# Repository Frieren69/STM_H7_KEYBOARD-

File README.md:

# STM_H7_KEYBOARD-
An keyboard with STM 32H7

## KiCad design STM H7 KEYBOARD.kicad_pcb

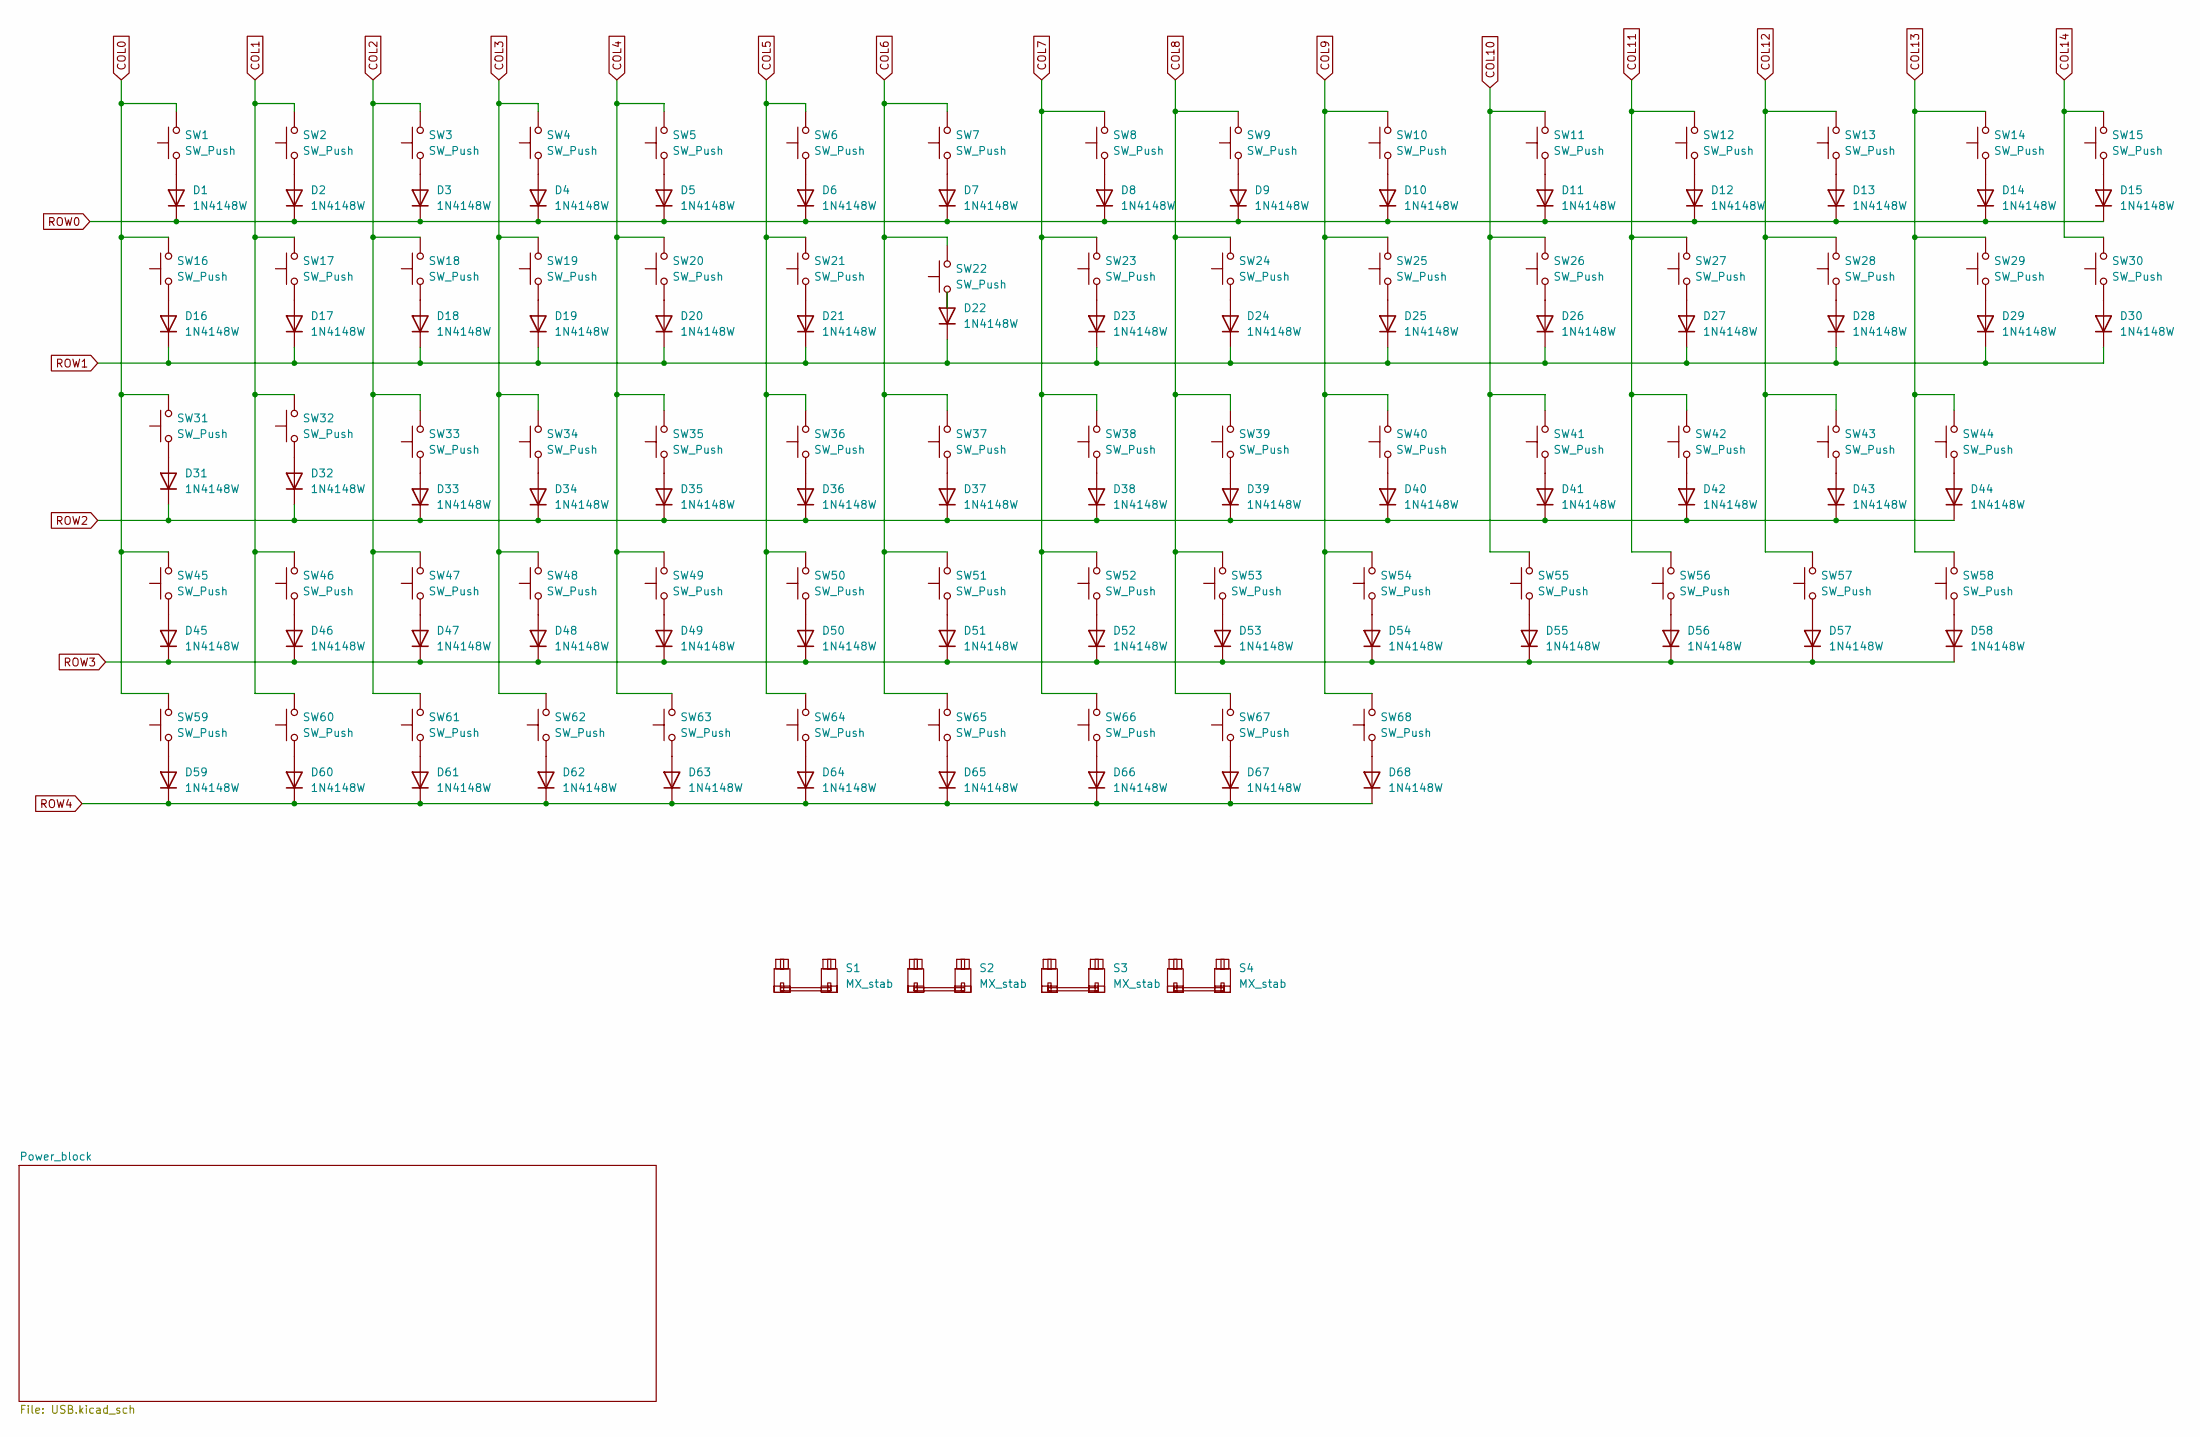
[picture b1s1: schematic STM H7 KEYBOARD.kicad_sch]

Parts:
D1, D2, D3, D4, D5, D6, D7, D8, D9, D10, D11, D12, D13, D14, D15, D16, D17, D18, D19, D20, D21, D22, D23, D24, D25, D26, D27, D28, D29, D30, D31, D32, D33, D34, D35, D36, D37, D38, D39, D40, D41, D42, D43, D44, D45, D46, D47, D48, D49, D50, D51, D52, D53, D54, D55, D56, D57, D58, D59, D60, D61, D62, D63, D64, D65, D66, D67, D68: 1N4148W; D_SOD-123
S1: MX_stab; STAB_MX_P_6.25u
S2, S3, S4: MX_stab; STAB_MX_P_2u
SW1, SW2, SW3, SW4, SW5, SW6, SW7, SW8, SW9, SW10, SW11, SW12, SW13, SW14, SW15, SW16, SW17, SW18, SW19, SW20, SW21, SW22, SW23, SW24, SW25, SW26, SW27, SW28, SW29, SW30, SW31, SW32, SW33, SW34, SW35, SW36, SW37, SW38, SW39, SW40, SW41, SW42, SW43, SW44, SW45, SW46, SW47, SW48, SW49, SW50, SW51, SW52, SW53, SW54, SW55, SW56, SW57, SW58, SW59, SW60, SW61, SW62, SW63, SW64, SW65, SW66, SW67, SW68: SW_Push; SW_MX_Hotswap_C49352235_5Pin

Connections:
COL0: SW1.2, SW16.2, SW31.2, SW45.2, SW59.2; also elsewhere on the board
COL2: SW3.2, SW18.2, SW33.2, SW47.2, SW61.2; also elsewhere on the board
COL3: SW4.2, SW19.2, SW34.2, SW48.2, SW62.2; also elsewhere on the board
COL4: SW5.2, SW20.2, SW35.2, SW49.2, SW63.2; also elsewhere on the board
COL5: SW6.2, SW21.2, SW36.2, SW50.2, SW64.2; also elsewhere on the board
COL6: SW7.2, SW22.2, SW37.2, SW51.2, SW65.2; also elsewhere on the board
COL7: SW8.2, SW23.2, SW38.2, SW52.2, SW66.2; also elsewhere on the board
COL8: SW9.2, SW24.2, SW39.2, SW53.2, SW67.2; also elsewhere on the board
COL9: SW10.2, SW25.2, SW40.2, SW54.2, SW68.2; also elsewhere on the board
COL10: SW11.2, SW26.2, SW41.2, SW55.2; also elsewhere on the board
COL11: SW12.2, SW27.2, SW42.2, SW56.2; also elsewhere on the board
COL12: SW13.2, SW28.2, SW43.2, SW57.2; also elsewhere on the board
COL13: SW14.2, SW29.2, SW44.2, SW58.2; also elsewhere on the board
COL14: SW15.2, SW30.2; also elsewhere on the board
unnamed: D1.2 (A), SW1.1
unnamed: D2.2 (A), SW2.1
unnamed: D3.2 (A), SW3.1
unnamed: D4.2 (A), SW4.1
unnamed: D5.2 (A), SW5.1
unnamed: D6.2 (A), SW6.1
unnamed: D7.2 (A), SW7.1
unnamed: D8.2 (A), SW8.1
unnamed: D9.2 (A), SW9.1
unnamed: D10.2 (A), SW10.1
unnamed: D11.2 (A), SW11.1
unnamed: D12.2 (A), SW12.1
unnamed: D13.2 (A), SW13.1
unnamed: D14.2 (A), SW14.1
unnamed: D15.2 (A), SW15.1
unnamed: D16.2 (A), SW16.1
unnamed: D17.2 (A), SW17.1
unnamed: D18.2 (A), SW18.1
unnamed: D19.2 (A), SW19.1
unnamed: D20.2 (A), SW20.1
unnamed: D21.2 (A), SW21.1
unnamed: D22.2 (A), SW22.1
unnamed: D23.2 (A), SW23.1
unnamed: D24.2 (A), SW24.1
unnamed: D25.2 (A), SW25.1
unnamed: D26.2 (A), SW26.1
unnamed: D27.2 (A), SW27.1
unnamed: D28.2 (A), SW28.1
unnamed: D29.2 (A), SW29.1
unnamed: D30.2 (A), SW30.1
unnamed: D31.2 (A), SW31.1
unnamed: D32.2 (A), SW32.1
unnamed: D33.2 (A), SW33.1
unnamed: D34.2 (A), SW34.1
unnamed: D35.2 (A), SW35.1
unnamed: D36.2 (A), SW36.1
unnamed: D37.2 (A), SW37.1
unnamed: D38.2 (A), SW38.1
unnamed: D39.2 (A), SW39.1
unnamed: D40.2 (A), SW40.1
unnamed: D41.2 (A), SW41.1
unnamed: D42.2 (A), SW42.1
unnamed: D43.2 (A), SW43.1
unnamed: D44.2 (A), SW44.1
unnamed: D45.2 (A), SW45.1
unnamed: D46.2 (A), SW46.1
unnamed: D47.2 (A), SW47.1
unnamed: D48.2 (A), SW48.1
unnamed: D49.2 (A), SW49.1
unnamed: D50.2 (A), SW50.1
unnamed: D51.2 (A), SW51.1
unnamed: D52.2 (A), SW52.1
unnamed: D53.2 (A), SW53.1
unnamed: D54.2 (A), SW54.1
unnamed: D55.2 (A), SW55.1
unnamed: D56.2 (A), SW56.1
unnamed: D57.2 (A), SW57.1
unnamed: D58.2 (A), SW58.1
unnamed: D59.2 (A), SW59.1
unnamed: D61.2 (A), SW61.1
unnamed: D62.2 (A), SW62.1
unnamed: D63.2 (A), SW63.1
unnamed: D64.2 (A), SW64.1
unnamed: D65.2 (A), SW65.1
unnamed: D66.2 (A), SW66.1
unnamed: D67.2 (A), SW67.1
unnamed: D68.2 (A), SW68.1
ROW0: D1.1 (K), D2.1 (K), D3.1 (K), D4.1 (K), D5.1 (K), D6.1 (K), D7.1 (K), D8.1 (K), D9.1 (K), D10.1 (K), D11.1 (K), D12.1 (K), D13.1 (K), D14.1 (K), D15.1 (K); also elsewhere on the board
ROW1: D16.1 (K), D17.1 (K), D18.1 (K), D19.1 (K), D20.1 (K), D21.1 (K), D22.1 (K), D23.1 (K), D24.1 (K), D25.1 (K), D26.1 (K), D27.1 (K), D28.1 (K), D29.1 (K), D30.1 (K); also elsewhere on the board
ROW2: D31.1 (K), D32.1 (K), D33.1 (K), D34.1 (K), D35.1 (K), D36.1 (K), D37.1 (K), D38.1 (K), D39.1 (K), D40.1 (K), D41.1 (K), D42.1 (K), D43.1 (K), D44.1 (K); also elsewhere on the board
ROW3: D45.1 (K), D46.1 (K), D47.1 (K), D48.1 (K), D49.1 (K), D50.1 (K), D51.1 (K), D52.1 (K), D53.1 (K), D54.1 (K), D55.1 (K), D56.1 (K), D57.1 (K), D58.1 (K); also elsewhere on the board
ROW4: D59.1 (K), D60.1 (K), D61.1 (K), D62.1 (K), D63.1 (K), D64.1 (K), D65.1 (K), D66.1 (K), D67.1 (K), D68.1 (K); also elsewhere on the board

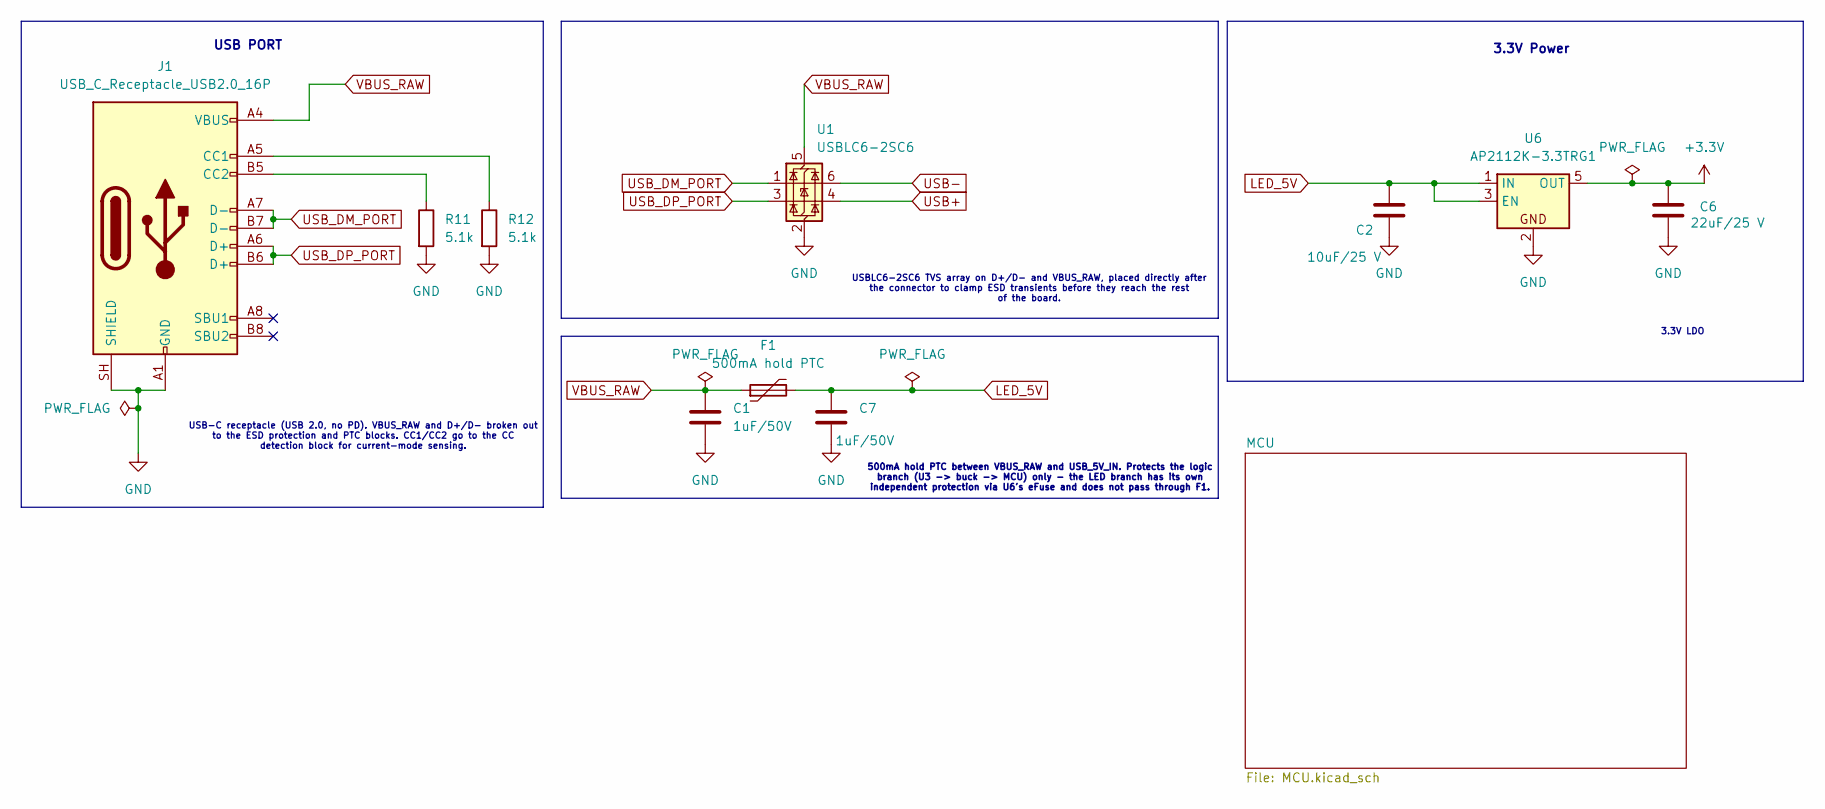
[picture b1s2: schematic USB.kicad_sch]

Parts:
C1, C7: 1uF/50V; C_0805_2012Metric
C2: 10uF/25 V; C_0805_2012Metric
C6: 22uF/25 V; C_0805_2012Metric
F1: 500mA hold PTC; Fuse_1206_3216Metric
J1: USB_C_Receptacle_USB2.0_16P; USB_C_Receptacle_HRO_TYPE-C-31-M-12
R11, R12: 5.1k; R_0603_1608Metric
U1: USBLC6-2SC6; SOT-23-6
U6: AP2112K-3.3TRG1; SOT-23-5

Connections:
+3.3V: C6.1, U6.5 (OUT); also elsewhere on the board
LED_5V: C2.1, C7.1, F1.2, U6.1 (IN), U6.3 (EN); also elsewhere on the board
unnamed: J1.A5 (CC1), R12.1
unnamed: J1.B5 (CC2), R11.1
USB+: U1.4 (I/O2); also elsewhere on the board
USB-: U1.6 (I/O1); also elsewhere on the board
USB_DM_PORT: J1.A7 (D-), J1.B7 (D-), U1.1 (I/O1)
USB_DP_PORT: J1.A6 (D+), J1.B6 (D+), U1.3 (I/O2)
VBUS_RAW: C1.1, F1.1, J1.A4 (VBUS), J1.A9 (VBUS), J1.B4 (VBUS), J1.B9 (VBUS), U1.5 (VBUS)

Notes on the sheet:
USBLC6-2SC6 TVS array on D+/D- and VBUS_RAW, placed directly after the connector to clamp ESD transients before they reach the rest of the board.
USB-C receptacle (USB 2.0, no PD). VBUS_RAW and D+/D- broken out to the ESD protection and PTC blocks. CC1/CC2 go to the CC detection block for current-mode sensing.
USB PORT
3.3V Power
500mA hold PTC between VBUS_RAW and USB_5V_IN. Protects the logic branch (U3 -> buck -> MCU) only - the LED branch has its own independent protection via U6's eFuse and does not pass through F1.
3.3V LDO

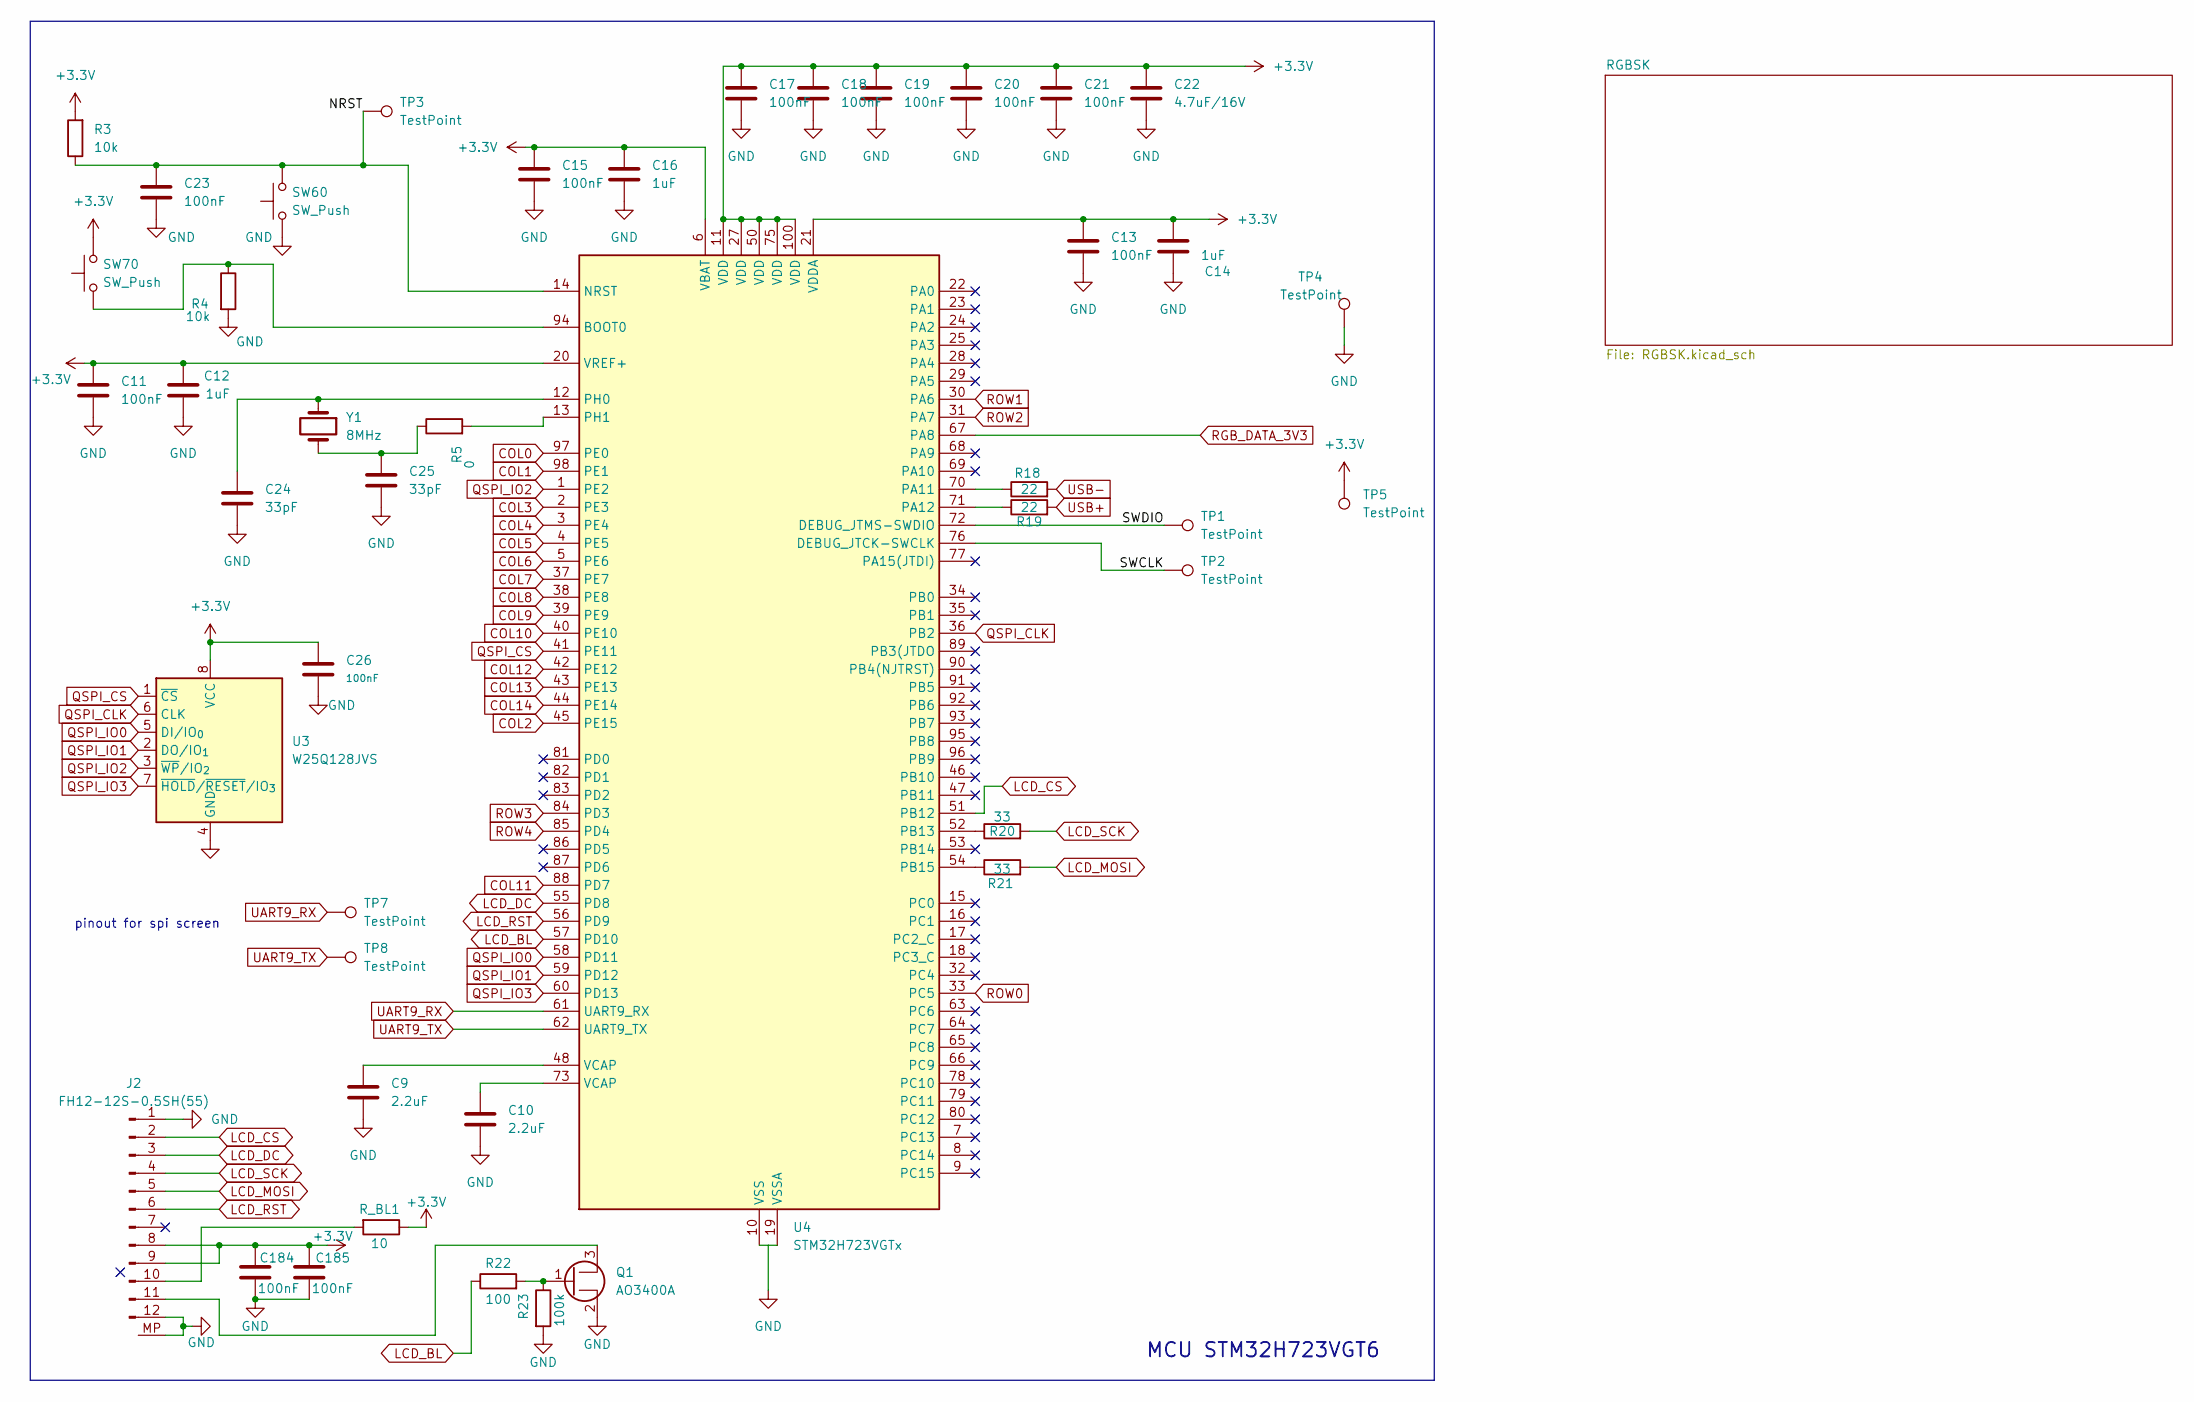
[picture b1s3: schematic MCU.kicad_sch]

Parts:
C9, C10: 2.2uF; C_0603_1608Metric
C11, C13, C15, C17, C18, C19, C20, C21, C23: 100nF; C_0603_1608Metric
C12, C14, C16: 1uF; C_0805_2012Metric
C22: 4.7uF/16V; C_0603_1608Metric
C24, C25: 33pF; C_0603_1608Metric
C26: 100nF; C_0402_1005Metric
C184, C185: 100nF; C_0402_1005Metric; LCSC C1525
J2: FH12-12S-0.5SH(55); Hirose_FH12-12S-0.5SH_1x12-1MP_P0.50mm_Horizontal; LCSC C88360
Q1: AO3400A; SOT-23; LCSC C20917
R3, R4: 10k; R_0603_1608Metric
R5: 0; R_0603_1608Metric
R18, R19: 22; R_0603_1608Metric
R20, R21: 33; R_0402_1005Metric; LCSC C25106
R22: 100; R_0402_1005Metric; LCSC C25076
R23: 100k; R_0402_1005Metric; LCSC C25741
R_BL1: 10; R_0603_1608Metric; LCSC C22859
SW60, SW70: SW_Push; SW_SPST_TL3342
TP1, TP2, TP3, TP4, TP5, TP7, TP8: TestPoint; TestPoint_Pad_D2.0mm
U3: W25Q128JVS; SOIC-8_5.3x5.3mm_P1.27mm; LCSC C97521
U4: STM32H723VGTx; LQFP-100_14x14mm_P0.5mm; LCSC C730142
Y1: 8MHz; Crystal_SMD_5032-2Pin_5.0x3.2mm; LCSC C115962

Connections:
+3.3V: C11.1, C12.1, C13.1, C14.1, C15.1, C16.1, C17.1, C18.1, C19.1, C20.1, C21.1, C22.1, C26.1, C184.1, C185.1, J2.8 (IOVCC), J2.9 (VCC), R3.2, R_BL1.1, TP5.1 (1_1), U3.8 (VCC), U4.6 (VBAT), U4.11 (VDD), U4.20 (VREF+), U4.21 (VDDA), U4.27 (VDD), U4.50 (VDD), U4.75 (VDD), U4.100 (VDD); also elsewhere on the board
/Power_block/MCU/SWCLK: TP2.1 (1_1), U4.76 (DEBUG_JTCK-SWCLK)
/Power_block/MCU/SWDIO: TP1.1 (1_1), U4.72 (DEBUG_JTMS-SWDIO)
COL0: U4.97 (PE0); also elsewhere on the board
COL2: U4.45 (PE15); also elsewhere on the board
COL3: U4.2 (PE3); also elsewhere on the board
COL4: U4.3 (PE4); also elsewhere on the board
COL5: U4.4 (PE5); also elsewhere on the board
COL6: U4.5 (PE6); also elsewhere on the board
COL7: U4.37 (PE7); also elsewhere on the board
COL8: U4.38 (PE8); also elsewhere on the board
COL9: U4.39 (PE9); also elsewhere on the board
COL10: U4.40 (PE10); also elsewhere on the board
COL11: U4.88 (PD7); also elsewhere on the board
COL12: U4.42 (PE12); also elsewhere on the board
COL13: U4.43 (PE13); also elsewhere on the board
COL14: U4.44 (PE14); also elsewhere on the board
LCD_BL: R22.1, U4.57 (PD10)
LCD_CS: J2.2 (CS), U4.51 (PB12)
LCD_DC: J2.3 (RS), U4.55 (PD8)
LCD_MOSI: J2.5 (SDA), R21.2
LCD_RST: J2.6 (RST), U4.56 (PD9)
LCD_SCK: J2.4 (SCL), R20.2
unnamed: C9.1, U4.48 (VCAP)
unnamed: C10.1, U4.73 (VCAP)
unnamed: C25.1, R5.1, Y1.2
unnamed 164: J2.10 (LEDA), R_BL1.2; also elsewhere on the board
unnamed: J2.11 (LEDK), Q1.3 (D)
unnamed: Q1.1 (G), R22.2, R23.1
unnamed 168: R4.1, U4.94 (BOOT0); also elsewhere on the board
unnamed: R18.1, U4.70 (PA11)
unnamed: R19.1, U4.71 (PA12)
unnamed: R20.1, U4.52 (PB13)
unnamed: R21.1, U4.54 (PB15)
unnamed: C24.1, U4.12 (PH0), Y1.1
unnamed: R5.2, U4.13 (PH1)
QSPI_CLK: U3.6 (CLK), U4.36 (PB2)
QSPI_CS: U3.1 (~CS), U4.41 (PE11)
QSPI_IO0: U3.5 (DI/IO_{0}), U4.58 (PD11)
QSPI_IO1: U3.2 (DO/IO_{1}), U4.59 (PD12)
QSPI_IO2: U3.3 (~WP/IO_{2}), U4.1 (PE2)
QSPI_IO3: U3.7 (~HOLD/~RESET/IO_{3}), U4.60 (PD13)
RGB_DATA_3V3: U4.67 (PA8); also elsewhere on the board
ROW0: U4.33 (PC5); also elsewhere on the board
ROW1: U4.30 (PA6); also elsewhere on the board
ROW2: U4.31 (PA7); also elsewhere on the board
ROW3: U4.84 (PD3); also elsewhere on the board
ROW4: U4.85 (PD4); also elsewhere on the board
UART9_RX: TP7.1 (1_1), U4.61 (UART9_RX)
UART9_TX: TP8.1 (1_1), U4.62 (UART9_TX)
USB+: R19.2; also elsewhere on the board
USB-: R18.2; also elsewhere on the board

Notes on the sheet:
pinout for spi screen
MCU STM32H723VGT6

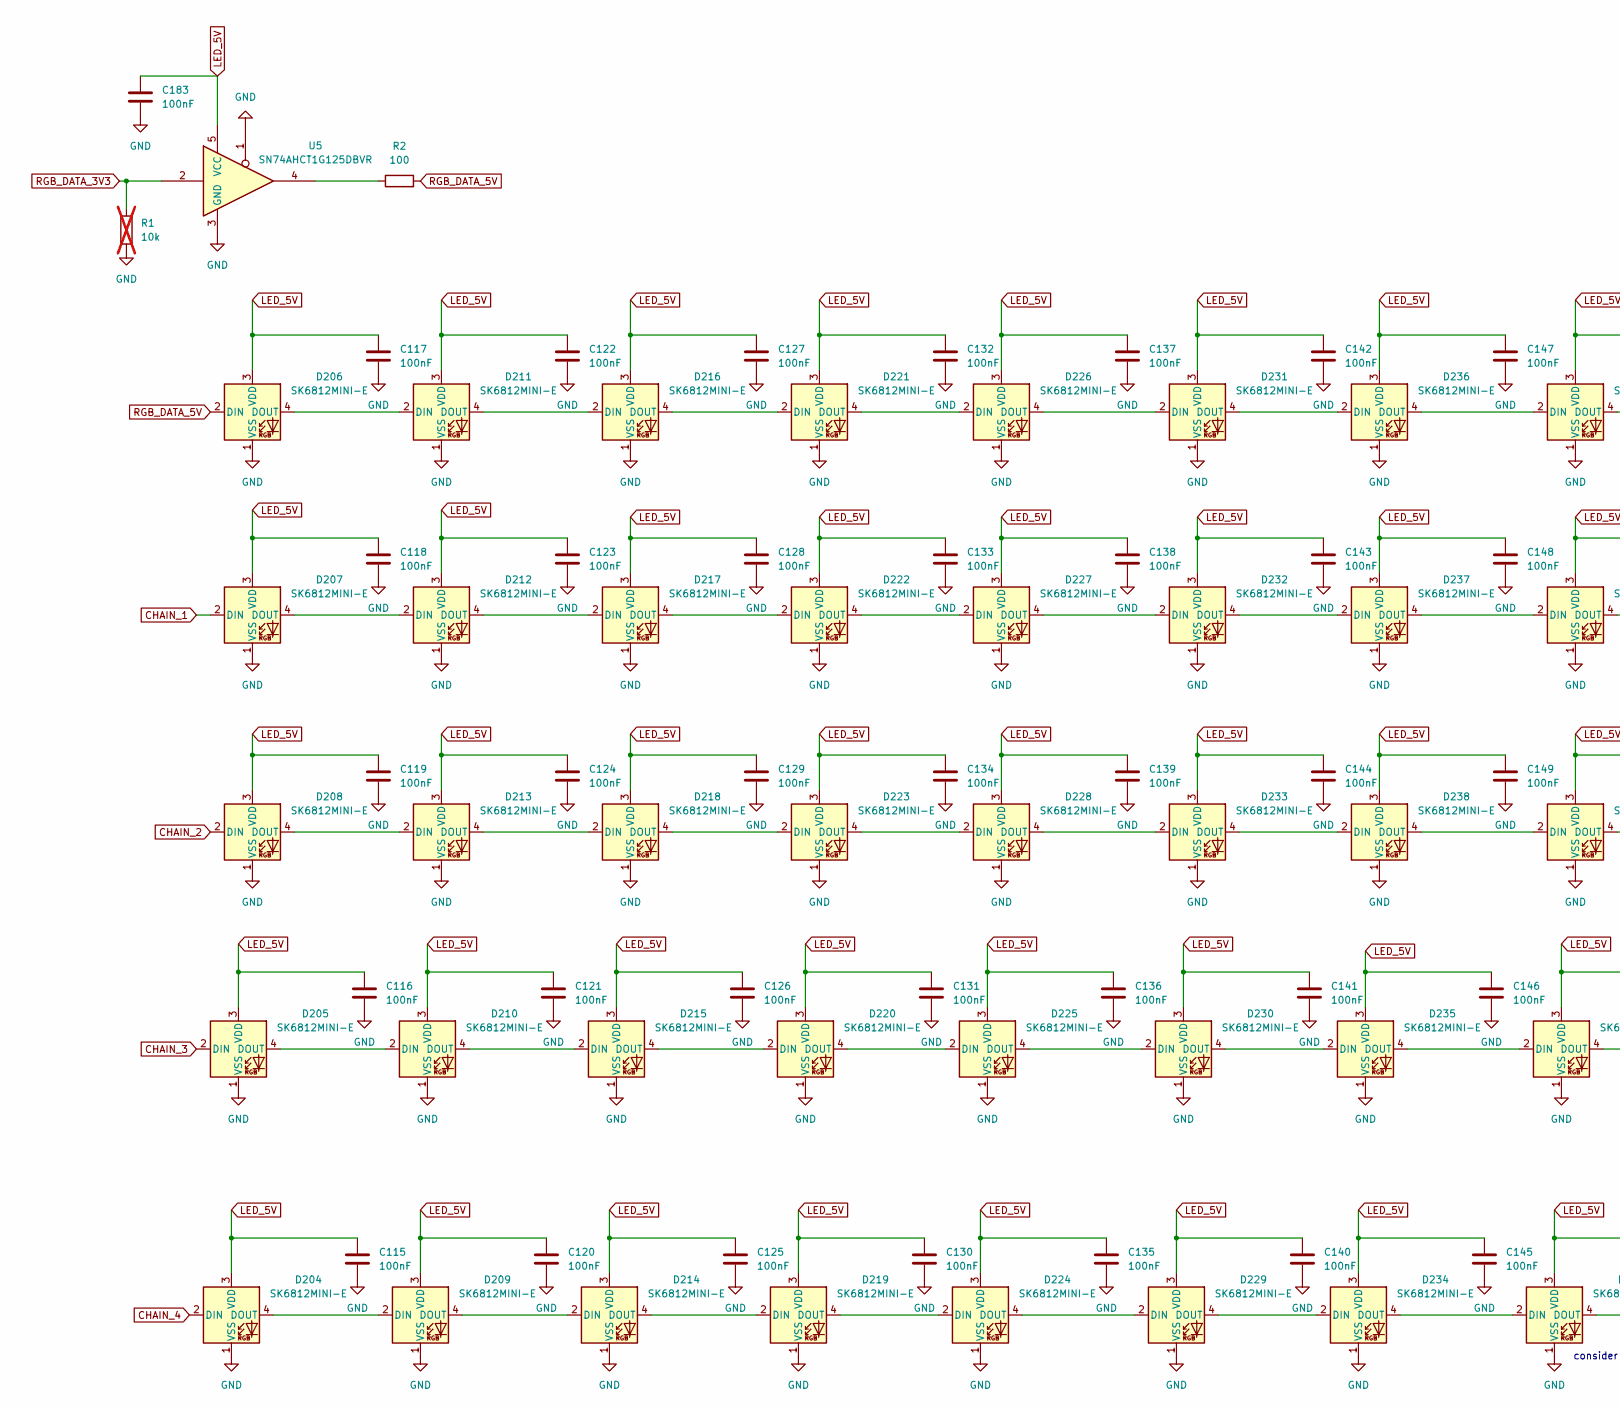
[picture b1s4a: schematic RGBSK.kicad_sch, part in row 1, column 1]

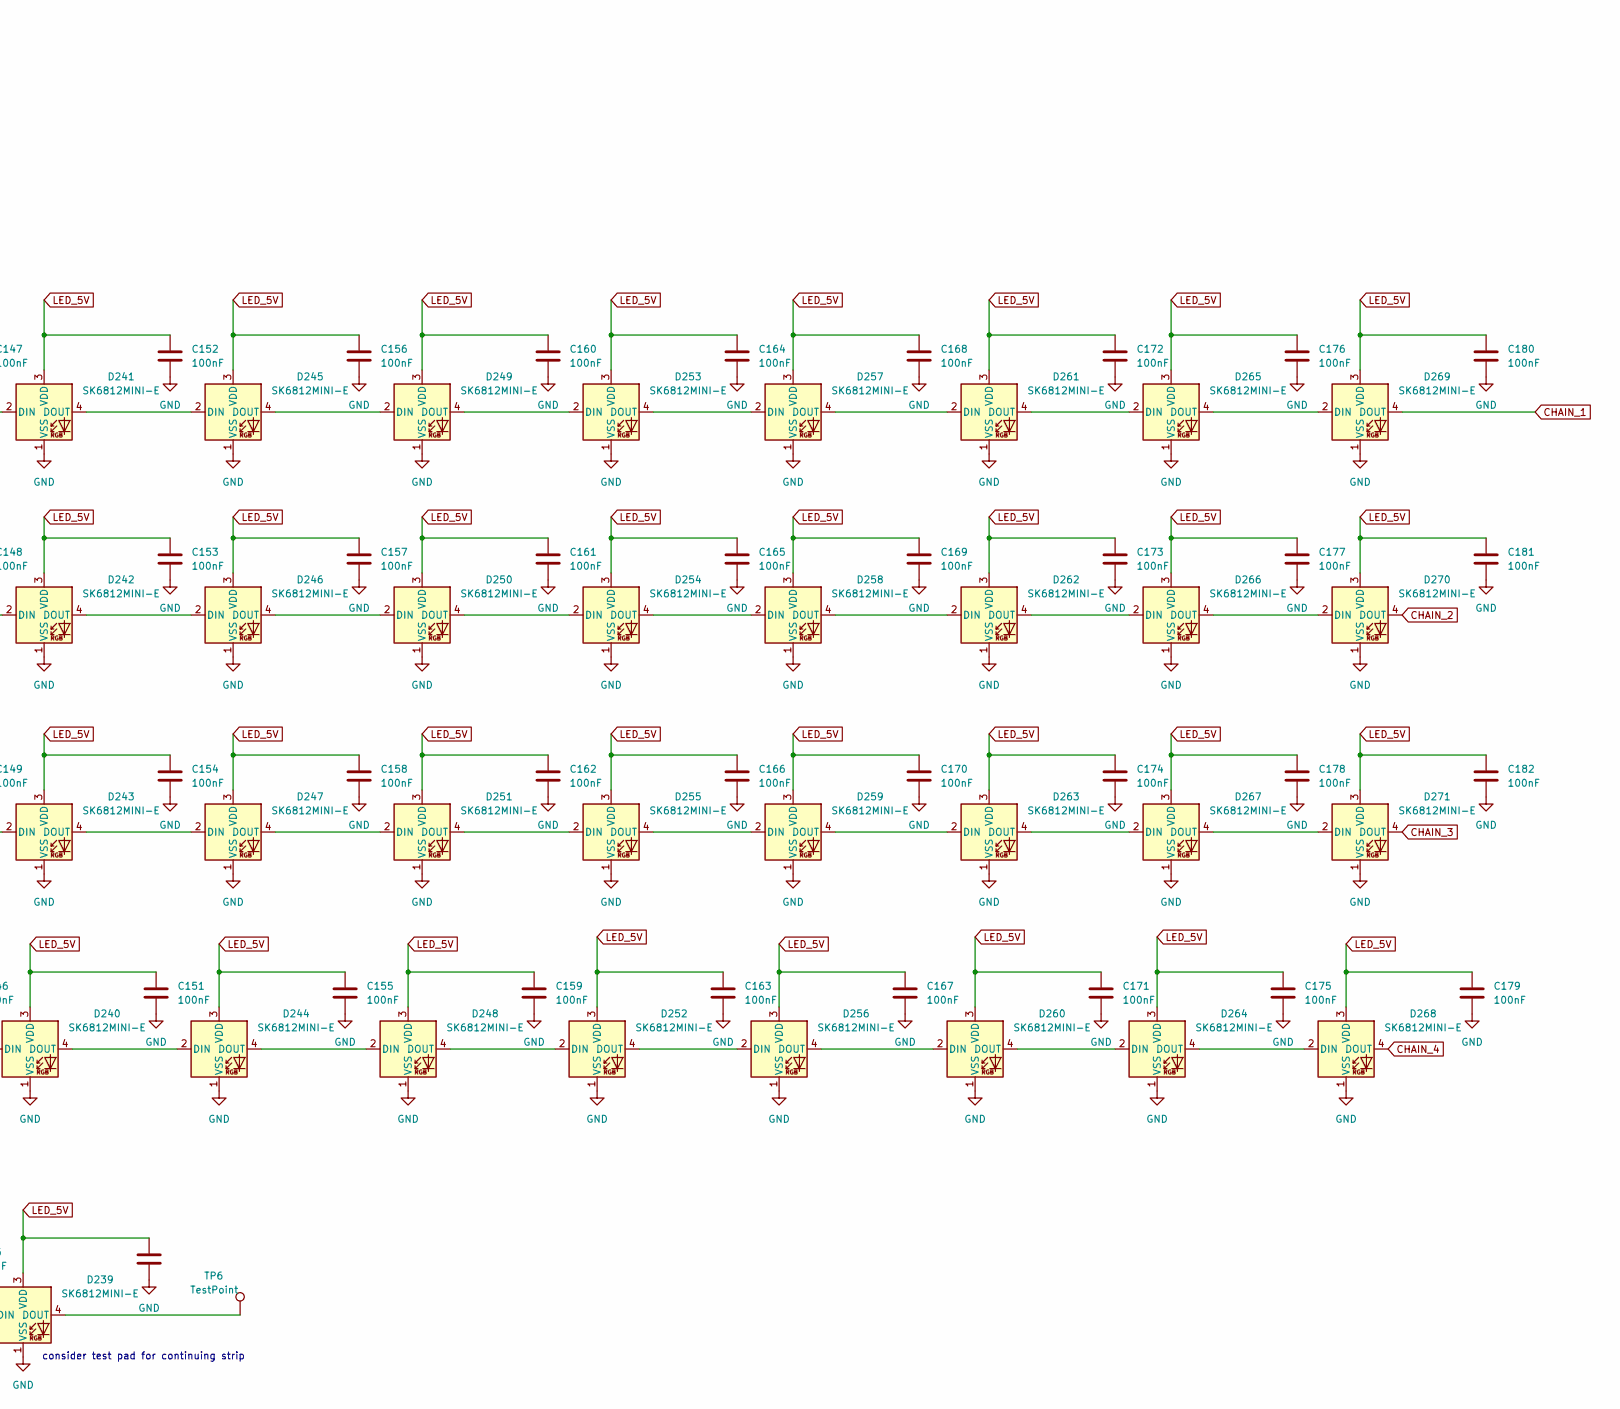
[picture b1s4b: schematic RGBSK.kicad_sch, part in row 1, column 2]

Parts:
C115, C116, C117, C118, C119, C120, C121, C122, C123, C124, C125, C126, C127, C128, C129, C130, C131, C132, C133, C134, C135, C136, C137, C138, C139, C140, C141, C142, C143, C144, C145, C146, C147, C148, C149, C150, C151, C152, C153, C154, C155, C156, C157, C158, C159, C160, C161, C162, C163, C164, C165, C166, C167, C168, C169, C170, C171, C172, C173, C174, C175, C176, C177, C178, C179, C180, C181, C182, C183: 100nF; C_0402_1005Metric
D204, D205, D206, D207, D208, D209, D210, D211, D212, D213, D214, D215, D216, D217, D218, D219, D220, D221, D222, D223, D224, D225, D226, D227, D228, D229, D230, D231, D232, D233, D234, D235, D236, D237, D238, D239, D240, D241, D242, D243, D244, D245, D246, D247, D248, D249, D250, D251, D252, D253, D254, D255, D256, D257, D258, D259, D260, D261, D262, D263, D264, D265, D266, D267, D268, D269, D270, D271: SK6812MINI-E; LED_SK6812MINI-E_3.2x2.8mm_P1.5mm_ReverseMount
R1: 10k; R_0402_1005Metric; not fitted
R2: 100; R_0402_1005Metric
TP6: TestPoint; TestPoint_Pad_D2.0mm
U5: SN74AHCT1G125DBVR; SOT-23-5

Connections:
CHAIN_1: D207.2 (DIN), D269.4 (DOUT)
CHAIN_2: D208.2 (DIN), D270.4 (DOUT)
CHAIN_3: D205.2 (DIN), D271.4 (DOUT)
CHAIN_4: D204.2 (DIN), D268.4 (DOUT)
LED_5V: C115.1, C116.1, C117.1, C118.1, C119.1, C120.1, C121.1, C122.1, C123.1, C124.1, C125.1, C126.1, C127.1, C128.1, C129.1, C130.1, C131.1, C132.1, C133.1, C134.1, C135.1, C136.1, C137.1, C138.1, C139.1, C140.1, C141.1, C142.1, C143.1, C144.1, C145.1, C146.1, C147.1, C148.1, C149.1, C150.1, C151.1, C152.1, C153.1, C154.1, C155.1, C156.1, C157.1, C158.1, C159.1, C160.1, C161.1, C162.1, C163.1, C164.1, C165.1, C166.1, C167.1, C168.1, C169.1, C170.1, C171.1, C172.1, C173.1, C174.1, C175.1, C176.1, C177.1, C178.1, C179.1, C180.1, C181.1, C182.1, C183.1, D204.3 (VDD), D205.3 (VDD), D206.3 (VDD), D207.3 (VDD), D208.3 (VDD), D209.3 (VDD), D210.3 (VDD), D211.3 (VDD), D212.3 (VDD), D213.3 (VDD), D214.3 (VDD), D215.3 (VDD), D216.3 (VDD), D217.3 (VDD), D218.3 (VDD), D219.3 (VDD), D220.3 (VDD), D221.3 (VDD), D222.3 (VDD), D223.3 (VDD), D224.3 (VDD), D225.3 (VDD), D226.3 (VDD), D227.3 (VDD), D228.3 (VDD), D229.3 (VDD), D230.3 (VDD), D231.3 (VDD), D232.3 (VDD), D233.3 (VDD), D234.3 (VDD), D235.3 (VDD), D236.3 (VDD), D237.3 (VDD), D238.3 (VDD), D239.3 (VDD), D240.3 (VDD), D241.3 (VDD), D242.3 (VDD), D243.3 (VDD), D244.3 (VDD), D245.3 (VDD), D246.3 (VDD), D247.3 (VDD), D248.3 (VDD), D249.3 (VDD), D250.3 (VDD), D251.3 (VDD), D252.3 (VDD), D253.3 (VDD), D254.3 (VDD), D255.3 (VDD), D256.3 (VDD), D257.3 (VDD), D258.3 (VDD), D259.3 (VDD), D260.3 (VDD), D261.3 (VDD), D262.3 (VDD), D263.3 (VDD), D264.3 (VDD), D265.3 (VDD), D266.3 (VDD), D267.3 (VDD), D268.3 (VDD), D269.3 (VDD), D270.3 (VDD), D271.3 (VDD), U5.5 (VCC); also elsewhere on the board
unnamed: D204.4 (DOUT), D209.2 (DIN)
unnamed: D205.4 (DOUT), D210.2 (DIN)
unnamed: D207.4 (DOUT), D212.2 (DIN)
unnamed: D208.4 (DOUT), D213.2 (DIN)
unnamed: D209.4 (DOUT), D214.2 (DIN)
unnamed: D210.4 (DOUT), D215.2 (DIN)
unnamed 104: D206.4 (DOUT), D211.2 (DIN); also elsewhere on the board
unnamed: D211.4 (DOUT), D216.2 (DIN)
unnamed: D212.4 (DOUT), D217.2 (DIN)
unnamed: D213.4 (DOUT), D218.2 (DIN)
unnamed: D214.4 (DOUT), D219.2 (DIN)
unnamed: D215.4 (DOUT), D220.2 (DIN)
unnamed: D216.4 (DOUT), D221.2 (DIN)
unnamed: D217.4 (DOUT), D222.2 (DIN)
unnamed: D218.4 (DOUT), D223.2 (DIN)
unnamed: D219.4 (DOUT), D224.2 (DIN)
unnamed: D220.4 (DOUT), D225.2 (DIN)
unnamed: D221.4 (DOUT), D226.2 (DIN)
unnamed: D222.4 (DOUT), D227.2 (DIN)
unnamed: D223.4 (DOUT), D228.2 (DIN)
unnamed: D224.4 (DOUT), D229.2 (DIN)
unnamed: D225.4 (DOUT), D230.2 (DIN)
unnamed: D226.4 (DOUT), D231.2 (DIN)
unnamed: D227.4 (DOUT), D232.2 (DIN)
unnamed: D228.4 (DOUT), D233.2 (DIN)
unnamed: D229.4 (DOUT), D234.2 (DIN)
unnamed: D230.4 (DOUT), D235.2 (DIN)
unnamed: D231.4 (DOUT), D236.2 (DIN)
unnamed: D232.4 (DOUT), D237.2 (DIN)
unnamed: D233.4 (DOUT), D238.2 (DIN)
unnamed: D234.4 (DOUT), D239.2 (DIN)
unnamed: D235.4 (DOUT), D240.2 (DIN)
unnamed: D236.4 (DOUT), D241.2 (DIN)
unnamed: D237.4 (DOUT), D242.2 (DIN)
unnamed: D238.4 (DOUT), D243.2 (DIN)
unnamed: D239.4 (DOUT), TP6.1 (1_1)
unnamed: D240.4 (DOUT), D244.2 (DIN)
unnamed: D241.4 (DOUT), D245.2 (DIN)
unnamed: D242.4 (DOUT), D246.2 (DIN)
unnamed: D243.4 (DOUT), D247.2 (DIN)
unnamed: D244.4 (DOUT), D248.2 (DIN)
unnamed: D245.4 (DOUT), D249.2 (DIN)
unnamed: D246.4 (DOUT), D250.2 (DIN)
unnamed: D247.4 (DOUT), D251.2 (DIN)
unnamed: D248.4 (DOUT), D252.2 (DIN)
unnamed: D249.4 (DOUT), D253.2 (DIN)
unnamed: D250.4 (DOUT), D254.2 (DIN)
unnamed: D251.4 (DOUT), D255.2 (DIN)
unnamed: D252.4 (DOUT), D256.2 (DIN)
unnamed: D253.4 (DOUT), D257.2 (DIN)
unnamed: D254.4 (DOUT), D258.2 (DIN)
unnamed: D255.4 (DOUT), D259.2 (DIN)
unnamed: D256.4 (DOUT), D260.2 (DIN)
unnamed: D257.4 (DOUT), D261.2 (DIN)
unnamed: D258.4 (DOUT), D262.2 (DIN)
unnamed: D259.4 (DOUT), D263.2 (DIN)
unnamed: D260.4 (DOUT), D264.2 (DIN)
unnamed: D261.4 (DOUT), D265.2 (DIN)
unnamed: D262.4 (DOUT), D266.2 (DIN)
unnamed: D263.4 (DOUT), D267.2 (DIN)
unnamed: D264.4 (DOUT), D268.2 (DIN)
unnamed: D265.4 (DOUT), D269.2 (DIN)
unnamed: D266.4 (DOUT), D270.2 (DIN)
unnamed: D267.4 (DOUT), D271.2 (DIN)
unnamed: R2.1, U5.4
RGB_DATA_3V3: R1.1, U5.2; also elsewhere on the board
RGB_DATA_5V: D206.2 (DIN), R2.2; also elsewhere on the board

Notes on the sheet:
consider test pad for continuing strip

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
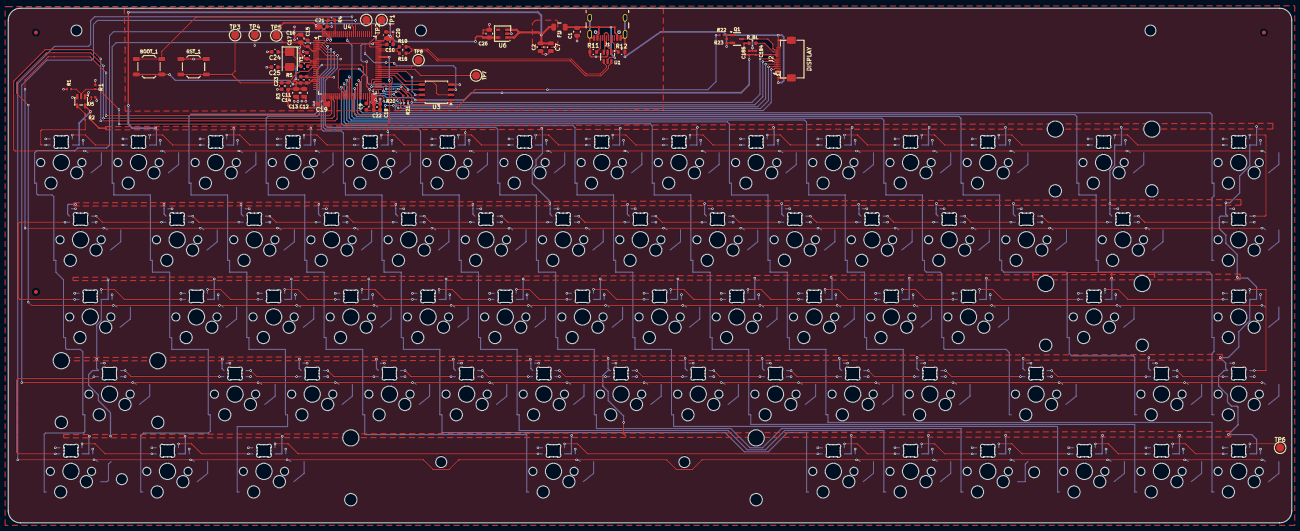
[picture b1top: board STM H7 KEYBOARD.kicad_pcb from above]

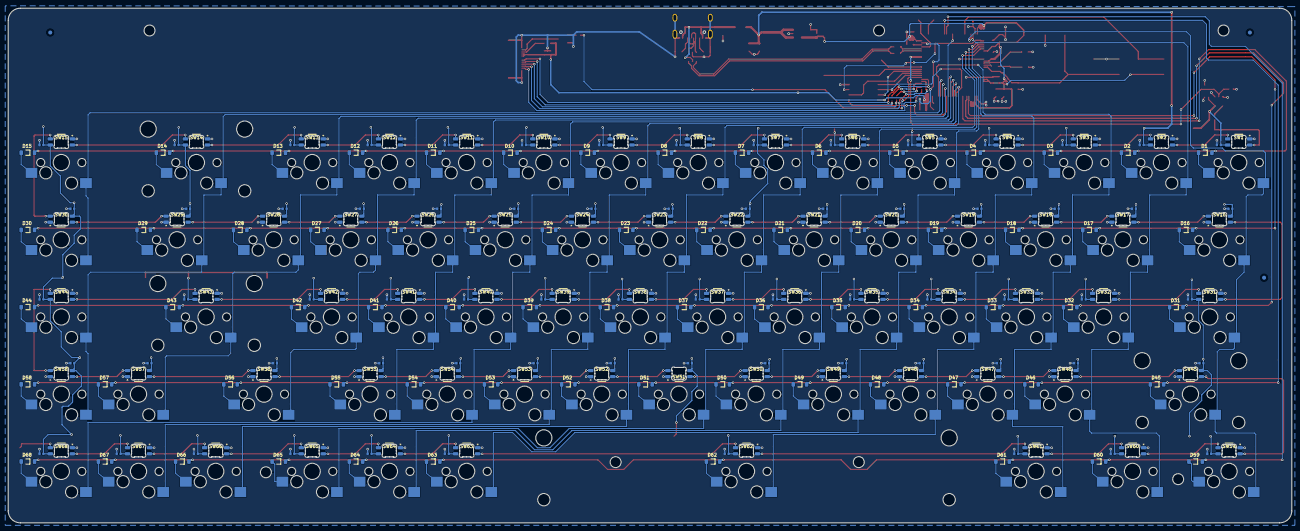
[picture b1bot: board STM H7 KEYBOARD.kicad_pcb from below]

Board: 2 copper layers, 316.7 x 127.0 mm, 349 parts (275 on the bottom side), 199 nets.

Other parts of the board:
BOOT_1: SW_Push; SW_SPST_TL3342
FID1, FID2, FID3, FID4, FID5, FID6: Fiducial_1mm_Mask2mm
H1, H2, H4, H5, H6, H7, H8: MountingHole; MountingHole_2.7mm_M2.5
LED1: SK6812MINI-E; LED_SK6812MINI-E_3.2x2.8mm_P1.5mm_ReverseMount
R1#2: 10k; R_0402_1005Metric
RST_1: SW_Push; SW_SPST_TL3342
R_BL: 10; R_0603_1608Metric

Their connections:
+3.3V: BOOT_1.2, R_BL.1; also elsewhere on the board
LED_5V: LED1.3 (VDD); also elsewhere on the board
unnamed 104: LED1.4 (DOUT); also elsewhere on the board
unnamed 164: R_BL.2; also elsewhere on the board
unnamed 168: BOOT_1.1; also elsewhere on the board
RGB_DATA_3V3: R1#2.1; also elsewhere on the board
RGB_DATA_5V: LED1.2 (DIN); also elsewhere on the board
